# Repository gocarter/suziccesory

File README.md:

# suziccesory

This project is an part of my college course.
All it is about, is to design and create device for anyone that have
an analogue motorcycle, and wants be able to gather some data from it.

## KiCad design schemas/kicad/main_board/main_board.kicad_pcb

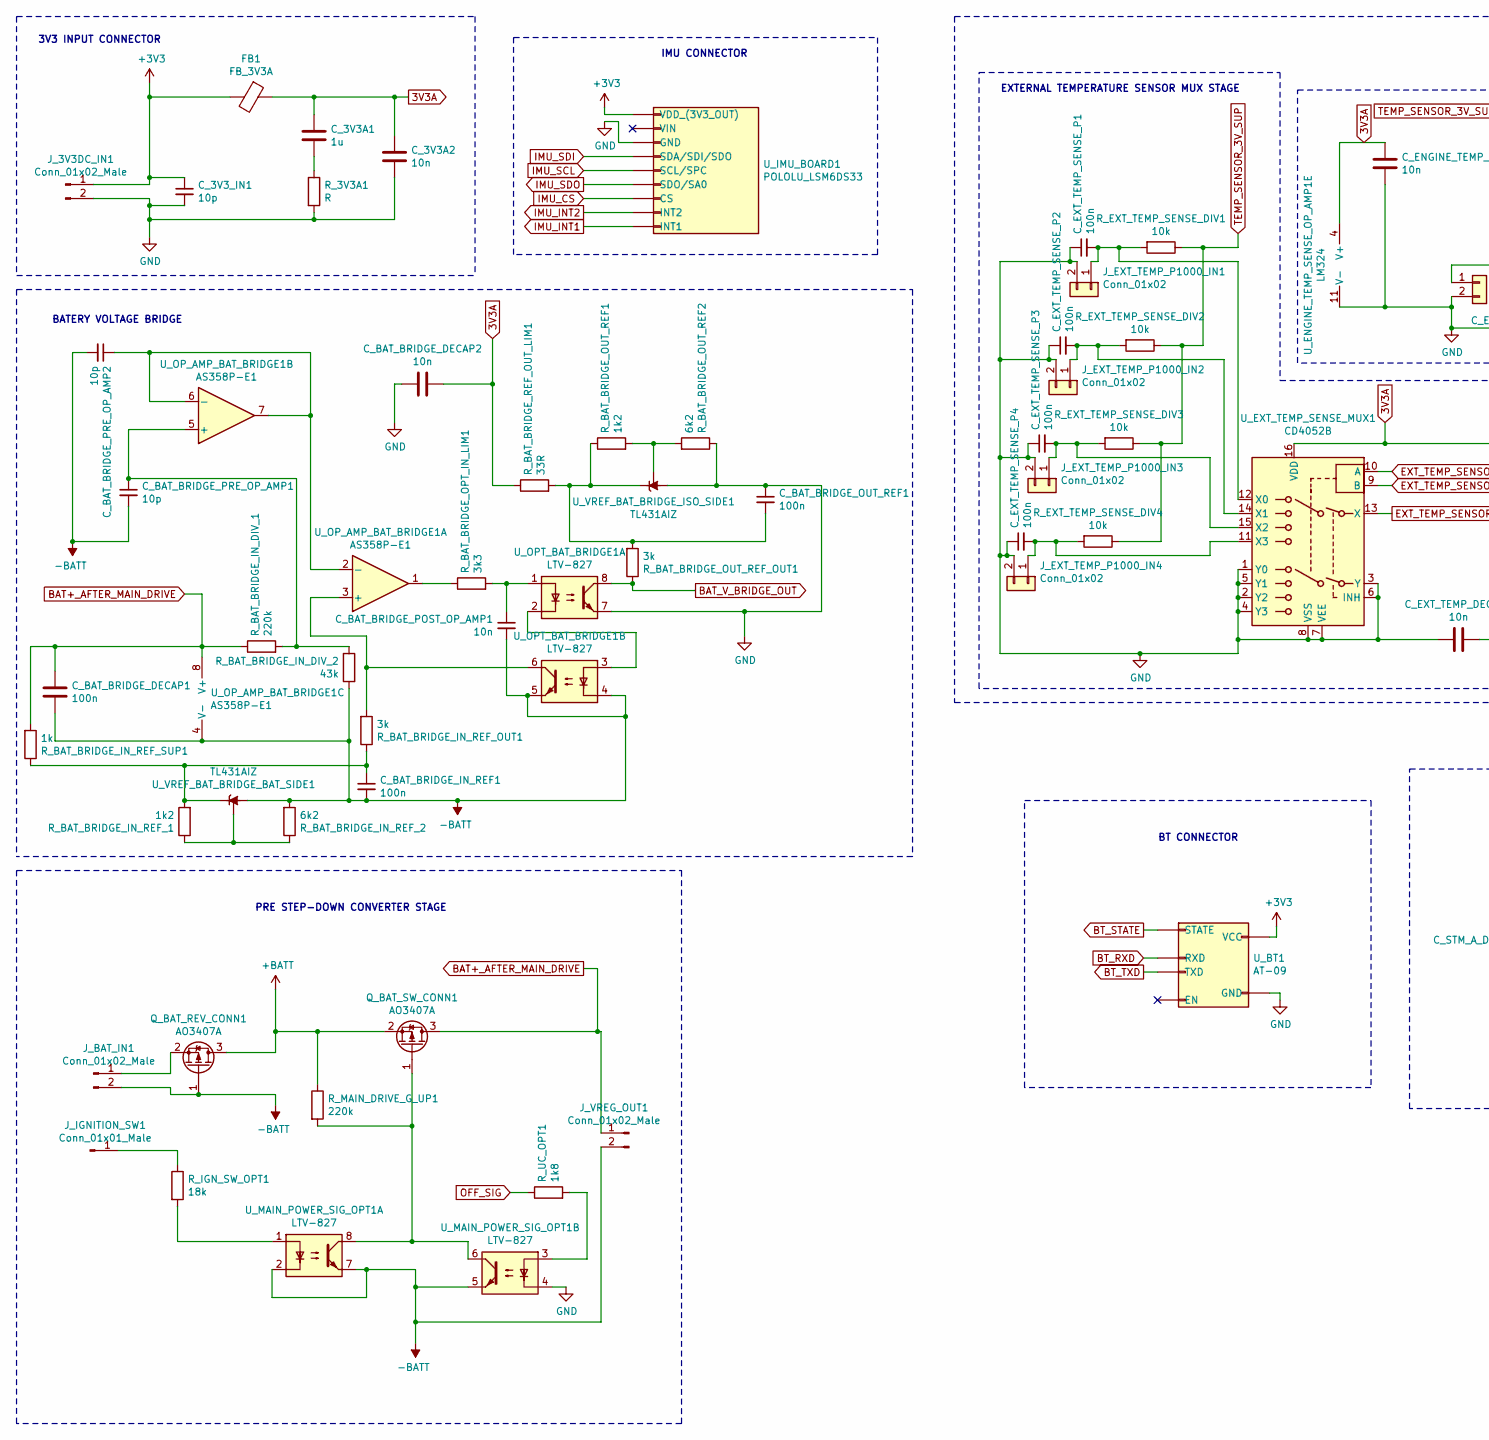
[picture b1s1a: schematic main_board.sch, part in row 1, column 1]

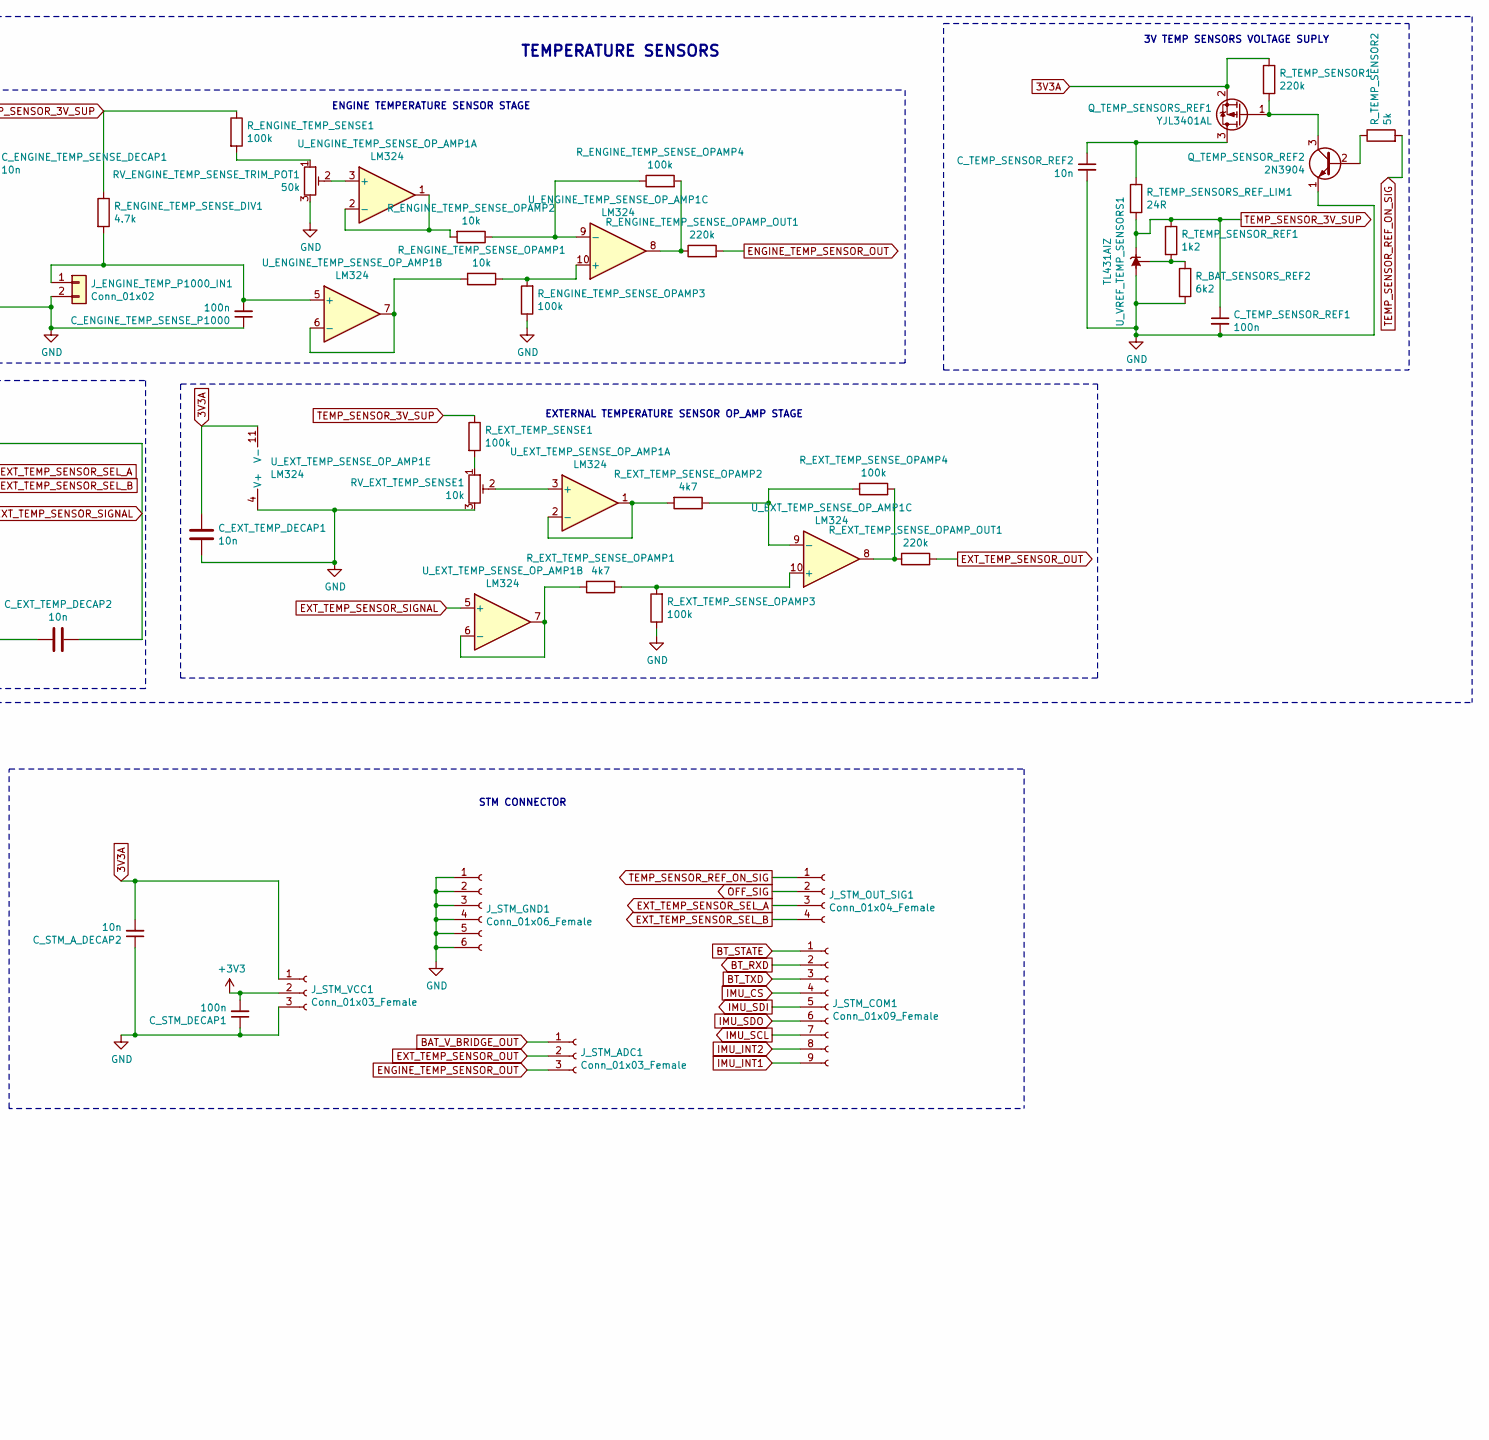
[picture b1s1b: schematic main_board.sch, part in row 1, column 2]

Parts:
C_3V3A1: 1u; C_Disc_D4.3mm_W1.9mm_P5.00mm
C_3V3A2: 10n; C_Disc_D3.0mm_W1.6mm_P2.50mm
C_3V3_IN1: 10p; C_Disc_D3.0mm_W1.6mm_P2.50mm
C_BAT_BRIDGE_DECAP1: 100n; C_Disc_D3.0mm_W1.6mm_P2.50mm
C_BAT_BRIDGE_DECAP2: 10n; C_Disc_D3.0mm_W1.6mm_P2.50mm
C_BAT_BRIDGE_IN_REF1: 100n; C_Disc_D3.0mm_W1.6mm_P2.50mm
C_BAT_BRIDGE_OUT_REF1: 100n; C_Disc_D3.0mm_W1.6mm_P2.50mm
C_BAT_BRIDGE_POST_OP_AMP1: 10n; C_Disc_D3.0mm_W1.6mm_P2.50mm
C_BAT_BRIDGE_PRE_OP_AMP1, C_BAT_BRIDGE_PRE_OP_AMP2: 10p; C_Disc_D3.0mm_W1.6mm_P2.50mm
C_ENGINE_TEMP_SENSE_DECAP1: 10n; C_Disc_D3.0mm_W1.6mm_P2.50mm
C_ENGINE_TEMP_SENSE_P1000: 100n; C_Disc_D3.0mm_W1.6mm_P2.50mm
C_EXT_TEMP_DECAP1, C_EXT_TEMP_DECAP2: 10n; C_Disc_D3.0mm_W1.6mm_P2.50mm
C_EXT_TEMP_SENSE_P1, C_EXT_TEMP_SENSE_P2, C_EXT_TEMP_SENSE_P3, C_EXT_TEMP_SENSE_P4: 100n; C_Disc_D3.0mm_W1.6mm_P2.50mm
C_STM_A_DECAP2: 10n; C_Disc_D3.0mm_W1.6mm_P2.50mm
C_STM_DECAP1: 100n; C_Disc_D3.0mm_W1.6mm_P2.50mm
C_TEMP_SENSOR_REF1: 100n; C_Disc_D3.0mm_W1.6mm_P2.50mm
C_TEMP_SENSOR_REF2: 10n; C_Disc_D3.0mm_W1.6mm_P2.50mm
FB1: FB_3V3A; R_Axial_DIN0204_L3.6mm_D1.6mm_P5.08mm_Horizontal
J_3V3DC_IN1: Conn_01x02_Male; PinHeader_1x02_P2.54mm_Vertical
J_BAT_IN1: Conn_01x02_Male; PinHeader_1x02_P2.54mm_Vertical
J_ENGINE_TEMP_P1000_IN1: Conn_01x02; PinHeader_1x02_P2.54mm_Vertical
J_EXT_TEMP_P1000_IN1, J_EXT_TEMP_P1000_IN2, J_EXT_TEMP_P1000_IN3, J_EXT_TEMP_P1000_IN4: Conn_01x02; PinHeader_1x02_P2.54mm_Vertical
J_IGNITION_SW1: Conn_01x01_Male; PinHeader_1x01_P2.54mm_Vertical
J_STM_ADC1: Conn_01x03_Female; PinSocket_1x03_P2.54mm_Vertical
J_STM_COM1: Conn_01x09_Female; PinSocket_1x09_P2.54mm_Vertical
J_STM_GND1: Conn_01x06_Female; PinSocket_1x06_P2.54mm_Vertical
J_STM_OUT_SIG1: Conn_01x04_Female; PinSocket_1x04_P2.54mm_Vertical
J_STM_VCC1: Conn_01x03_Female; PinSocket_1x03_P2.54mm_Vertical
J_VREG_OUT1: Conn_01x02_Male; PinHeader_1x02_P2.54mm_Vertical
Q_BAT_REV_CONN1: AO3407A; SOT-23
Q_BAT_SW_CONN1: AO3407A; SOT-23
Q_TEMP_SENSORS_REF1: YJL3401AL; SOT-23
Q_TEMP_SENSOR_REF2: 2N3904; TO-92_Inline
RV_ENGINE_TEMP_SENSE_TRIM_POT1: 50k; Potentiometer_Bourns_3296W_Vertical
RV_EXT_TEMP_SENSE1: 10k; Potentiometer_Bourns_3296W_Vertical
R_3V3A1: R; R_Axial_DIN0204_L3.6mm_D1.6mm_P5.08mm_Horizontal
R_BAT_BRIDGE_IN_DIV_1: 220k; R_Axial_DIN0204_L3.6mm_D1.6mm_P5.08mm_Horizontal
R_BAT_BRIDGE_IN_DIV_2: 43k; R_Axial_DIN0204_L3.6mm_D1.6mm_P5.08mm_Horizontal
R_BAT_BRIDGE_IN_REF_1: 1k2; R_Axial_DIN0204_L3.6mm_D1.6mm_P5.08mm_Horizontal
R_BAT_BRIDGE_IN_REF_2: 6k2; R_Axial_DIN0204_L3.6mm_D1.6mm_P5.08mm_Horizontal
R_BAT_BRIDGE_IN_REF_OUT1: 3k; R_Axial_DIN0204_L3.6mm_D1.6mm_P5.08mm_Horizontal
R_BAT_BRIDGE_IN_REF_SUP1: 1k; R_Axial_DIN0204_L3.6mm_D1.6mm_P5.08mm_Horizontal
R_BAT_BRIDGE_OPT_IN_LIM1: 3k3; R_Axial_DIN0204_L3.6mm_D1.6mm_P5.08mm_Horizontal
R_BAT_BRIDGE_OUT_REF1: 1k2; R_Axial_DIN0204_L3.6mm_D1.6mm_P5.08mm_Horizontal
R_BAT_BRIDGE_OUT_REF2: 6k2; R_Axial_DIN0204_L3.6mm_D1.6mm_P5.08mm_Horizontal
R_BAT_BRIDGE_OUT_REF_OUT1: 3k; R_Axial_DIN0204_L3.6mm_D1.6mm_P5.08mm_Horizontal
R_BAT_BRIDGE_REF_OUT_LIM1: 33R; R_Axial_DIN0204_L3.6mm_D1.6mm_P5.08mm_Horizontal
R_BAT_SENSORS_REF2: 6k2; R_Axial_DIN0204_L3.6mm_D1.6mm_P5.08mm_Horizontal
R_ENGINE_TEMP_SENSE1: 100k; R_Axial_DIN0204_L3.6mm_D1.6mm_P5.08mm_Horizontal
R_ENGINE_TEMP_SENSE_DIV1: 4.7k; R_Axial_DIN0204_L3.6mm_D1.6mm_P5.08mm_Horizontal
R_ENGINE_TEMP_SENSE_OPAMP1, R_ENGINE_TEMP_SENSE_OPAMP2: 10k; R_Axial_DIN0204_L3.6mm_D1.6mm_P5.08mm_Horizontal
R_ENGINE_TEMP_SENSE_OPAMP3, R_ENGINE_TEMP_SENSE_OPAMP4: 100k; R_Axial_DIN0204_L3.6mm_D1.6mm_P5.08mm_Horizontal
R_ENGINE_TEMP_SENSE_OPAMP_OUT1: 220k; R_Axial_DIN0204_L3.6mm_D1.6mm_P5.08mm_Horizontal
R_EXT_TEMP_SENSE1: 100k; R_Axial_DIN0204_L3.6mm_D1.6mm_P5.08mm_Horizontal
R_EXT_TEMP_SENSE_DIV1, R_EXT_TEMP_SENSE_DIV2, R_EXT_TEMP_SENSE_DIV3, R_EXT_TEMP_SENSE_DIV4: 10k; R_Axial_DIN0204_L3.6mm_D1.6mm_P5.08mm_Horizontal
R_EXT_TEMP_SENSE_OPAMP1, R_EXT_TEMP_SENSE_OPAMP2: 4k7; R_Axial_DIN0204_L3.6mm_D1.6mm_P5.08mm_Horizontal
R_EXT_TEMP_SENSE_OPAMP3, R_EXT_TEMP_SENSE_OPAMP4: 100k; R_Axial_DIN0204_L3.6mm_D1.6mm_P5.08mm_Horizontal
R_EXT_TEMP_SENSE_OPAMP_OUT1: 220k; R_Axial_DIN0204_L3.6mm_D1.6mm_P5.08mm_Horizontal
R_IGN_SW_OPT1: 18k; R_Axial_DIN0204_L3.6mm_D1.6mm_P5.08mm_Horizontal
R_MAIN_DRIVE_G_UP1: 220k; R_Axial_DIN0204_L3.6mm_D1.6mm_P5.08mm_Horizontal
R_TEMP_SENSOR1: 220k; R_Axial_DIN0204_L3.6mm_D1.6mm_P5.08mm_Horizontal
R_TEMP_SENSOR2: 5k; R_Axial_DIN0204_L3.6mm_D1.6mm_P5.08mm_Horizontal
R_TEMP_SENSORS_REF_LIM1: 24R; R_Axial_DIN0204_L3.6mm_D1.6mm_P5.08mm_Horizontal
R_TEMP_SENSOR_REF1: 1k2; R_Axial_DIN0204_L3.6mm_D1.6mm_P5.08mm_Horizontal
R_UC_OPT1: 1k8; R_Axial_DIN0204_L3.6mm_D1.6mm_P5.08mm_Horizontal
U_BT1: AT-09; PinHeader_1x06_P2.54mm_Vertical
U_ENGINE_TEMP_SENSE_OP_AMP1: LM324; DIP-14_W7.62mm
U_EXT_TEMP_SENSE_MUX1: CD4052B; DIP-16_W7.62mm_LongPads
U_EXT_TEMP_SENSE_OP_AMP1: LM324; DIP-14_W7.62mm_LongPads
U_IMU_BOARD1: POLOLU_LSM6DS33; PinHeader_1x09_P2.54mm_Vertical
U_MAIN_POWER_SIG_OPT1: LTV-827; DIP-8_W7.62mm
U_OPT_BAT_BRIDGE1: LTV-827; DIP-8_W7.62mm_LongPads
U_OP_AMP_BAT_BRIDGE1: AS358P-E1; DIP-8_W7.62mm_LongPads
U_VREF_BAT_BRIDGE_BAT_SIDE1: TL431AIZ; TO-92_Inline
U_VREF_BAT_BRIDGE_ISO_SIDE1: TL431AIZ; TO-92_Inline
U_VREF_TEMP_SENSORS1: TL431AIZ; TO-92_Inline

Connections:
3V3A: C_3V3A1.1, C_3V3A2.1, C_BAT_BRIDGE_DECAP2.1, C_ENGINE_TEMP_SENSE_DECAP1.1, C_EXT_TEMP_DECAP1.1, C_EXT_TEMP_DECAP2.1, C_STM_A_DECAP2.2, FB1.1, J_STM_VCC1.1, Q_TEMP_SENSORS_REF1.2 (S), R_BAT_BRIDGE_REF_OUT_LIM1.1, R_TEMP_SENSOR1.1, U_ENGINE_TEMP_SENSE_OP_AMP1.4 (V+), U_EXT_TEMP_SENSE_MUX1.16 (VDD), U_EXT_TEMP_SENSE_OP_AMP1.11 (V-)
+3V3: C_3V3_IN1.1, C_STM_DECAP1.2, FB1.2, J_3V3DC_IN1.1, J_STM_VCC1.2, U_BT1.5 (VCC), U_IMU_BOARD1.1 (VDD_(3V3_OUT))
+BATT: Q_BAT_REV_CONN1.3 (D), Q_BAT_SW_CONN1.2 (S), R_MAIN_DRIVE_G_UP1.1
-BATT: C_BAT_BRIDGE_DECAP1.2, C_BAT_BRIDGE_IN_REF1.2, C_BAT_BRIDGE_POST_OP_AMP1.2, C_BAT_BRIDGE_PRE_OP_AMP1.2, C_BAT_BRIDGE_PRE_OP_AMP2.2, J_BAT_IN1.2, J_VREG_OUT1.2, Q_BAT_REV_CONN1.1 (G), R_BAT_BRIDGE_IN_DIV_2.2, R_BAT_BRIDGE_IN_REF_2.2, U_MAIN_POWER_SIG_OPT1.2, U_MAIN_POWER_SIG_OPT1.5, U_MAIN_POWER_SIG_OPT1.7, U_OPT_BAT_BRIDGE1.4, U_OPT_BAT_BRIDGE1.5, U_OP_AMP_BAT_BRIDGE1.4 (V-), U_VREF_BAT_BRIDGE_BAT_SIDE1.2 (A)
BAT+_AFTER_MAIN_DRIVE: C_BAT_BRIDGE_DECAP1.1, J_VREG_OUT1.1, Q_BAT_SW_CONN1.3 (D), R_BAT_BRIDGE_IN_DIV_1.1, R_BAT_BRIDGE_IN_REF_SUP1.2, U_OP_AMP_BAT_BRIDGE1.8 (V+)
BAT_V_BRIDGE_OUT: J_STM_ADC1.1, R_BAT_BRIDGE_OUT_REF_OUT1.1, U_OPT_BAT_BRIDGE1.8
BT_RXD: J_STM_COM1.2, U_BT1.2 (RXD)
BT_STATE: J_STM_COM1.1, U_BT1.1 (STATE)
BT_TXD: J_STM_COM1.3, U_BT1.3 (TXD)
ENGINE_TEMP_SENSOR_OUT: J_STM_ADC1.3, R_ENGINE_TEMP_SENSE_OPAMP_OUT1.2
EXT_TEMP_SENSOR_OUT: J_STM_ADC1.2, R_EXT_TEMP_SENSE_OPAMP_OUT1.2
EXT_TEMP_SENSOR_SEL_A: J_STM_OUT_SIG1.3, U_EXT_TEMP_SENSE_MUX1.10 (A)
EXT_TEMP_SENSOR_SEL_B: J_STM_OUT_SIG1.4, U_EXT_TEMP_SENSE_MUX1.9 (B)
EXT_TEMP_SENSOR_SIGNAL: U_EXT_TEMP_SENSE_MUX1.13 (X), U_EXT_TEMP_SENSE_OP_AMP1.5 (+)
GND: C_3V3A2.2, C_3V3_IN1.2, C_BAT_BRIDGE_DECAP2.2, C_BAT_BRIDGE_OUT_REF1.1, C_ENGINE_TEMP_SENSE_DECAP1.2, C_ENGINE_TEMP_SENSE_P1000.1, C_EXT_TEMP_DECAP1.2, C_EXT_TEMP_DECAP2.2, C_EXT_TEMP_SENSE_P1.1, C_EXT_TEMP_SENSE_P2.1, C_EXT_TEMP_SENSE_P3.1, C_EXT_TEMP_SENSE_P4.1, C_STM_A_DECAP2.1, C_STM_DECAP1.1, C_TEMP_SENSOR_REF1.2, C_TEMP_SENSOR_REF2.2, J_3V3DC_IN1.2, J_ENGINE_TEMP_P1000_IN1.2, J_EXT_TEMP_P1000_IN1.2, J_EXT_TEMP_P1000_IN2.2, J_EXT_TEMP_P1000_IN3.2, J_EXT_TEMP_P1000_IN4.2, J_STM_GND1.1, J_STM_GND1.2, J_STM_GND1.3, J_STM_GND1.4, J_STM_GND1.5, J_STM_GND1.6, J_STM_VCC1.3, Q_TEMP_SENSOR_REF2.1 (E), RV_ENGINE_TEMP_SENSE_TRIM_POT1.3, RV_EXT_TEMP_SENSE1.3, R_3V3A1.2, R_BAT_BRIDGE_OUT_REF2.1, R_BAT_SENSORS_REF2.2, R_ENGINE_TEMP_SENSE_OPAMP3.1, R_EXT_TEMP_SENSE_OPAMP3.1, U_BT1.4 (GND), U_ENGINE_TEMP_SENSE_OP_AMP1.11 (V-), U_EXT_TEMP_SENSE_MUX1.1 (Y0), U_EXT_TEMP_SENSE_MUX1.2 (Y2), U_EXT_TEMP_SENSE_MUX1.3 (Y), U_EXT_TEMP_SENSE_MUX1.4 (Y3), U_EXT_TEMP_SENSE_MUX1.5 (Y1), U_EXT_TEMP_SENSE_MUX1.6 (INH), U_EXT_TEMP_SENSE_MUX1.7 (VEE), U_EXT_TEMP_SENSE_MUX1.8 (VSS), U_EXT_TEMP_SENSE_OP_AMP1.4 (V+), U_IMU_BOARD1.3 (GND), U_MAIN_POWER_SIG_OPT1.4, U_OPT_BAT_BRIDGE1.7, U_VREF_BAT_BRIDGE_ISO_SIDE1.2 (A), U_VREF_TEMP_SENSORS1.2 (A)
IMU_CS: J_STM_COM1.4, U_IMU_BOARD1.7 (CS)
IMU_INT1: J_STM_COM1.9, U_IMU_BOARD1.9 (INT1)
IMU_INT2: J_STM_COM1.8, U_IMU_BOARD1.8 (INT2)
IMU_SCL: J_STM_COM1.7, U_IMU_BOARD1.5 (SCL/SPC)
IMU_SDI: J_STM_COM1.5, U_IMU_BOARD1.4 (SDA/SDI/SDO)
IMU_SDO: J_STM_COM1.6, U_IMU_BOARD1.6 (SDO/SA0)
unnamed: C_3V3A1.2, R_3V3A1.1
unnamed: C_BAT_BRIDGE_IN_REF1.1, R_BAT_BRIDGE_IN_REF_1.2, R_BAT_BRIDGE_IN_REF_OUT1.1, R_BAT_BRIDGE_IN_REF_SUP1.1, U_VREF_BAT_BRIDGE_BAT_SIDE1.3 (K)
unnamed: C_BAT_BRIDGE_OUT_REF1.2, R_BAT_BRIDGE_OUT_REF1.1, R_BAT_BRIDGE_OUT_REF_OUT1.2, R_BAT_BRIDGE_REF_OUT_LIM1.2, U_VREF_BAT_BRIDGE_ISO_SIDE1.3 (K)
unnamed: C_BAT_BRIDGE_POST_OP_AMP1.1, R_BAT_BRIDGE_OPT_IN_LIM1.2, U_OPT_BAT_BRIDGE1.1
unnamed: C_BAT_BRIDGE_PRE_OP_AMP1.1, R_BAT_BRIDGE_IN_DIV_1.2, R_BAT_BRIDGE_IN_DIV_2.1, U_OP_AMP_BAT_BRIDGE1.5 (+)
unnamed: C_BAT_BRIDGE_PRE_OP_AMP2.1, U_OP_AMP_BAT_BRIDGE1.2 (-), U_OP_AMP_BAT_BRIDGE1.6 (-), U_OP_AMP_BAT_BRIDGE1.7
unnamed: C_ENGINE_TEMP_SENSE_P1000.2, J_ENGINE_TEMP_P1000_IN1.1, R_ENGINE_TEMP_SENSE_DIV1.2, U_ENGINE_TEMP_SENSE_OP_AMP1.5 (+)
unnamed: C_EXT_TEMP_SENSE_P1.2, J_EXT_TEMP_P1000_IN1.1, R_EXT_TEMP_SENSE_DIV1.2, U_EXT_TEMP_SENSE_MUX1.12 (X0)
unnamed: C_EXT_TEMP_SENSE_P2.2, J_EXT_TEMP_P1000_IN2.1, R_EXT_TEMP_SENSE_DIV2.2, U_EXT_TEMP_SENSE_MUX1.14 (X1)
unnamed: C_EXT_TEMP_SENSE_P3.2, J_EXT_TEMP_P1000_IN3.1, R_EXT_TEMP_SENSE_DIV3.2, U_EXT_TEMP_SENSE_MUX1.15 (X2)
unnamed: C_EXT_TEMP_SENSE_P4.2, J_EXT_TEMP_P1000_IN4.1, R_EXT_TEMP_SENSE_DIV4.2, U_EXT_TEMP_SENSE_MUX1.11 (X3)
unnamed: C_TEMP_SENSOR_REF2.1, Q_TEMP_SENSORS_REF1.3 (D), R_TEMP_SENSORS_REF_LIM1.1
unnamed: J_BAT_IN1.1, Q_BAT_REV_CONN1.2 (S)
unnamed: J_IGNITION_SW1.1, R_IGN_SW_OPT1.1
unnamed: Q_BAT_SW_CONN1.1 (G), R_MAIN_DRIVE_G_UP1.2, U_MAIN_POWER_SIG_OPT1.6, U_MAIN_POWER_SIG_OPT1.8
unnamed: Q_TEMP_SENSORS_REF1.1 (G), Q_TEMP_SENSOR_REF2.3 (C), R_TEMP_SENSOR1.2
unnamed: Q_TEMP_SENSOR_REF2.2 (B), R_TEMP_SENSOR2.1
unnamed: RV_ENGINE_TEMP_SENSE_TRIM_POT1.1, R_ENGINE_TEMP_SENSE1.2
unnamed: RV_ENGINE_TEMP_SENSE_TRIM_POT1.2, U_ENGINE_TEMP_SENSE_OP_AMP1.3 (+)
unnamed: RV_EXT_TEMP_SENSE1.1, R_EXT_TEMP_SENSE1.2
unnamed: RV_EXT_TEMP_SENSE1.2, U_EXT_TEMP_SENSE_OP_AMP1.3 (+)
unnamed: R_BAT_BRIDGE_IN_REF_1.1, R_BAT_BRIDGE_IN_REF_2.1, U_VREF_BAT_BRIDGE_BAT_SIDE1.1 (REF)
unnamed: R_BAT_BRIDGE_IN_REF_OUT1.2, U_OPT_BAT_BRIDGE1.6, U_OP_AMP_BAT_BRIDGE1.3 (+)
unnamed: R_BAT_BRIDGE_OPT_IN_LIM1.1, U_OP_AMP_BAT_BRIDGE1.1
unnamed: R_BAT_BRIDGE_OUT_REF1.2, R_BAT_BRIDGE_OUT_REF2.2, U_VREF_BAT_BRIDGE_ISO_SIDE1.1 (REF)
unnamed: R_BAT_SENSORS_REF2.1, R_TEMP_SENSOR_REF1.2, U_VREF_TEMP_SENSORS1.1 (REF)
unnamed: R_ENGINE_TEMP_SENSE_OPAMP1.1, R_ENGINE_TEMP_SENSE_OPAMP3.2, U_ENGINE_TEMP_SENSE_OP_AMP1.10 (+)
unnamed: R_ENGINE_TEMP_SENSE_OPAMP1.2, U_ENGINE_TEMP_SENSE_OP_AMP1.6 (-), U_ENGINE_TEMP_SENSE_OP_AMP1.7
unnamed: R_ENGINE_TEMP_SENSE_OPAMP2.1, R_ENGINE_TEMP_SENSE_OPAMP4.1, U_ENGINE_TEMP_SENSE_OP_AMP1.9 (-)
unnamed: R_ENGINE_TEMP_SENSE_OPAMP2.2, U_ENGINE_TEMP_SENSE_OP_AMP1.1, U_ENGINE_TEMP_SENSE_OP_AMP1.2 (-)
unnamed: R_ENGINE_TEMP_SENSE_OPAMP4.2, R_ENGINE_TEMP_SENSE_OPAMP_OUT1.1, U_ENGINE_TEMP_SENSE_OP_AMP1.8
unnamed: R_EXT_TEMP_SENSE_OPAMP1.1, R_EXT_TEMP_SENSE_OPAMP3.2, U_EXT_TEMP_SENSE_OP_AMP1.10 (+)
unnamed: R_EXT_TEMP_SENSE_OPAMP1.2, U_EXT_TEMP_SENSE_OP_AMP1.6 (-), U_EXT_TEMP_SENSE_OP_AMP1.7
unnamed: R_EXT_TEMP_SENSE_OPAMP2.1, R_EXT_TEMP_SENSE_OPAMP4.1, U_EXT_TEMP_SENSE_OP_AMP1.9 (-)
unnamed: R_EXT_TEMP_SENSE_OPAMP2.2, U_EXT_TEMP_SENSE_OP_AMP1.1, U_EXT_TEMP_SENSE_OP_AMP1.2 (-)
unnamed: R_EXT_TEMP_SENSE_OPAMP4.2, R_EXT_TEMP_SENSE_OPAMP_OUT1.1, U_EXT_TEMP_SENSE_OP_AMP1.8
unnamed: R_IGN_SW_OPT1.2, U_MAIN_POWER_SIG_OPT1.1
unnamed: R_UC_OPT1.2, U_MAIN_POWER_SIG_OPT1.3
unnamed: U_OPT_BAT_BRIDGE1.2, U_OPT_BAT_BRIDGE1.3
OFF_SIG: J_STM_OUT_SIG1.2, R_UC_OPT1.1
TEMP_SENSOR_3V_SUP: C_TEMP_SENSOR_REF1.1, R_ENGINE_TEMP_SENSE1.1, R_ENGINE_TEMP_SENSE_DIV1.1, R_EXT_TEMP_SENSE1.1, R_EXT_TEMP_SENSE_DIV1.1, R_EXT_TEMP_SENSE_DIV2.1, R_EXT_TEMP_SENSE_DIV3.1, R_EXT_TEMP_SENSE_DIV4.1, R_TEMP_SENSORS_REF_LIM1.2, R_TEMP_SENSOR_REF1.1, U_VREF_TEMP_SENSORS1.3 (K)
TEMP_SENSOR_REF_ON_SIG: J_STM_OUT_SIG1.1, R_TEMP_SENSOR2.2

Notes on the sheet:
PRE STEP-DOWN CONVERTER STAGE
BATERY VOLTAGE BRIDGE
3V3 INPUT CONNECTOR
3V TEMP SENSORS VOLTAGE SUPLY
ENGINE TEMPERATURE SENSOR STAGE
IMU CONNECTOR
EXTERNAL TEMPERATURE SENSOR OP_AMP STAGE
EXTERNAL TEMPERATURE SENSOR MUX STAGE
TEMPERATURE SENSORS
BT CONNECTOR
STM CONNECTOR

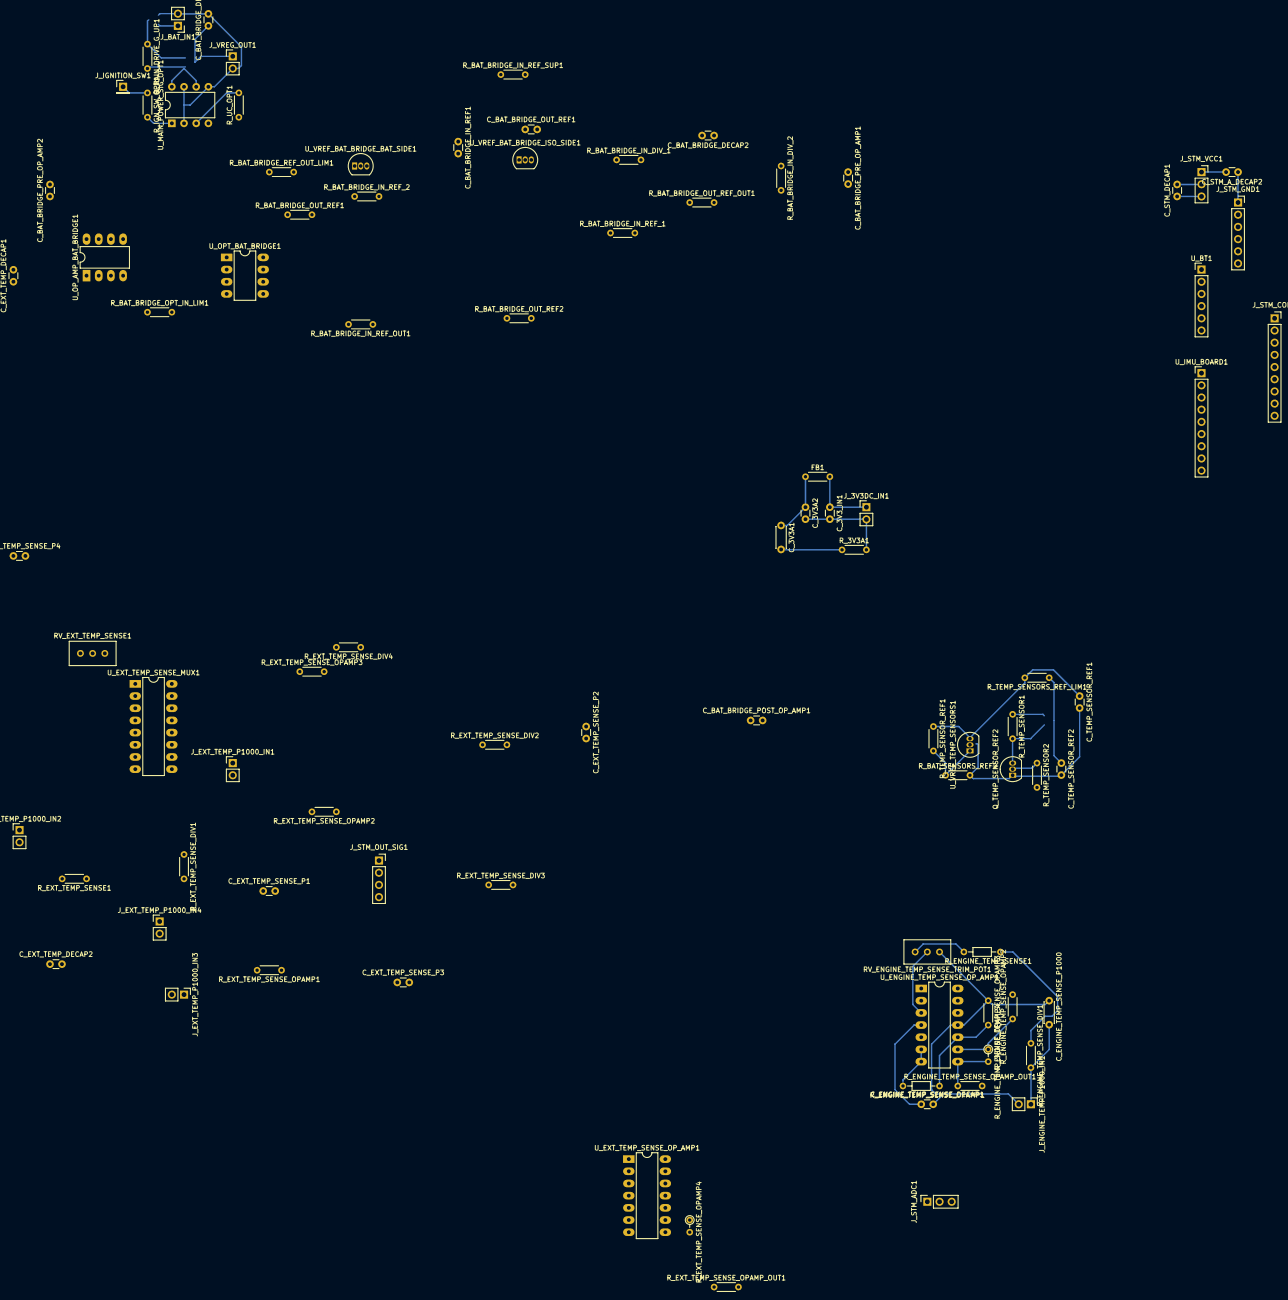
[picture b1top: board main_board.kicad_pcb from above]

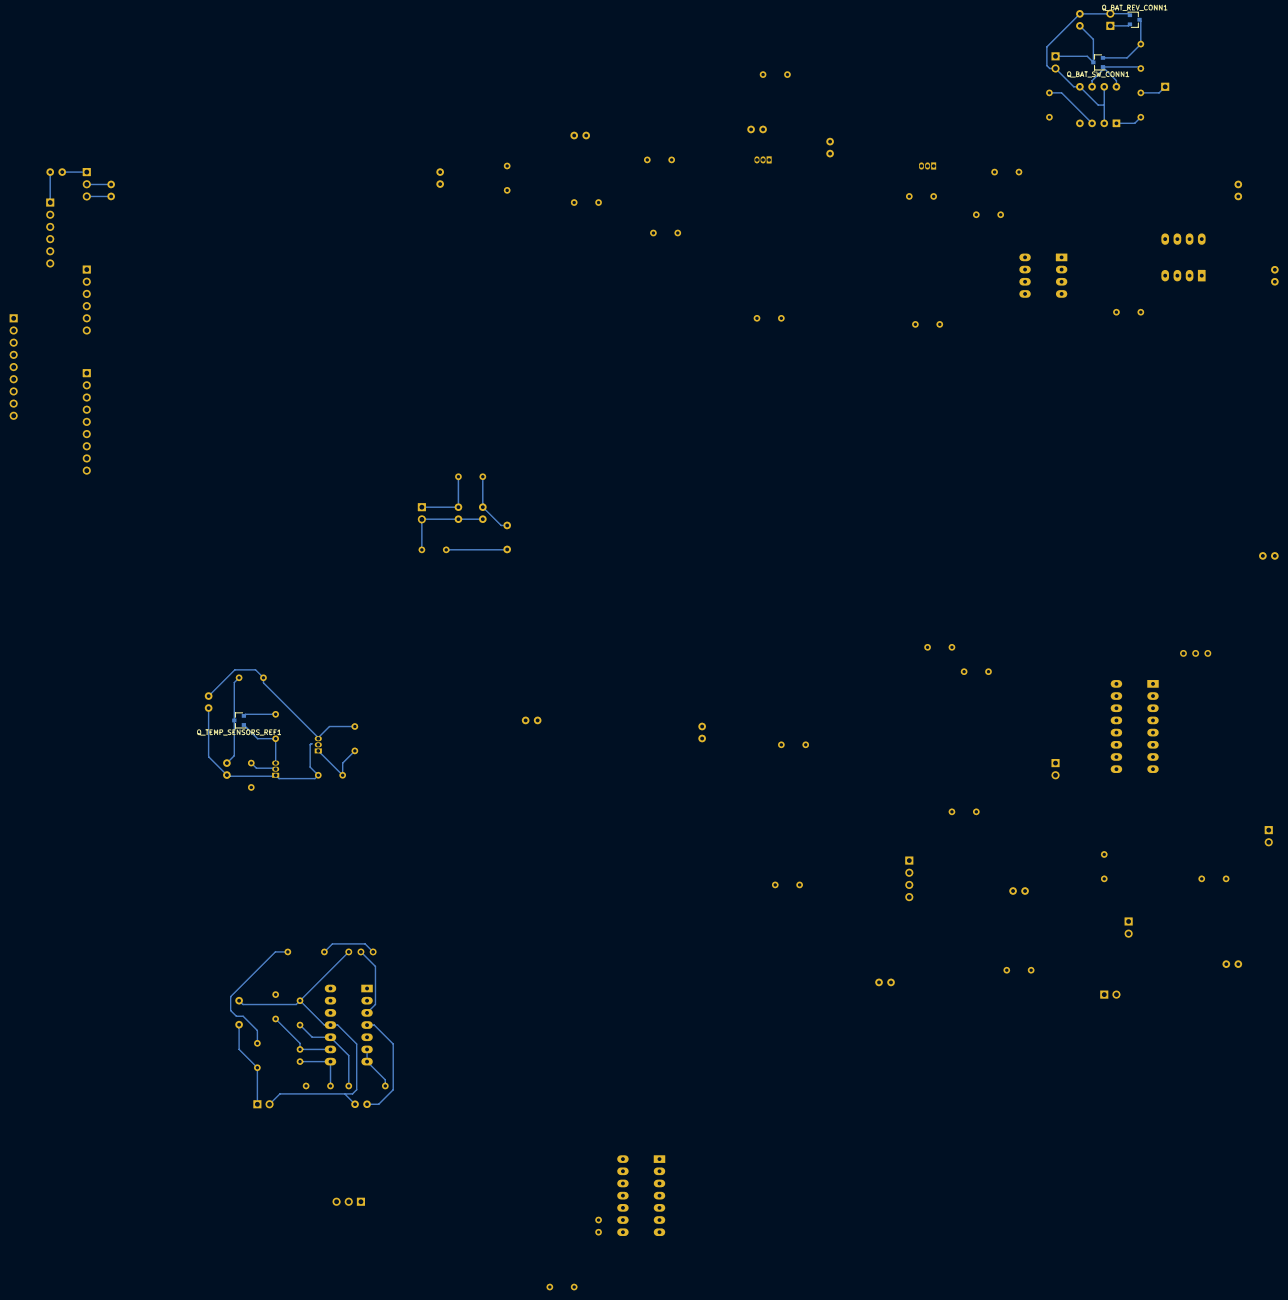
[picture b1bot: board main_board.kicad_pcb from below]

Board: 2 copper layers, 91 parts (3 on the bottom side), 63 nets.

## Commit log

2020-10-23 Added some deneral docs and gitignore file.
2020-10-23 Removed autosave Dia file
2020-11-09 Added first version of electric schema made in kicad. Connections to STM NUCLEO board yet to be done.
2020-11-10 Initial board file was created. NUCLEO board symbol was removed, and now there are female pin connectors in place of it. For simplicity reasons, and because of wrong footprint included in this lib.
2020-11-12 From now on login with ssh
2020-11-12 This project is no longer part of my engineering thesis
